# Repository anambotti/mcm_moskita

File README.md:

# pcb_16ccd_module
16-CCD module

# Create a newq branch 
git checkout -b branchName

# Move back to master branch
git checkout master

# List branches

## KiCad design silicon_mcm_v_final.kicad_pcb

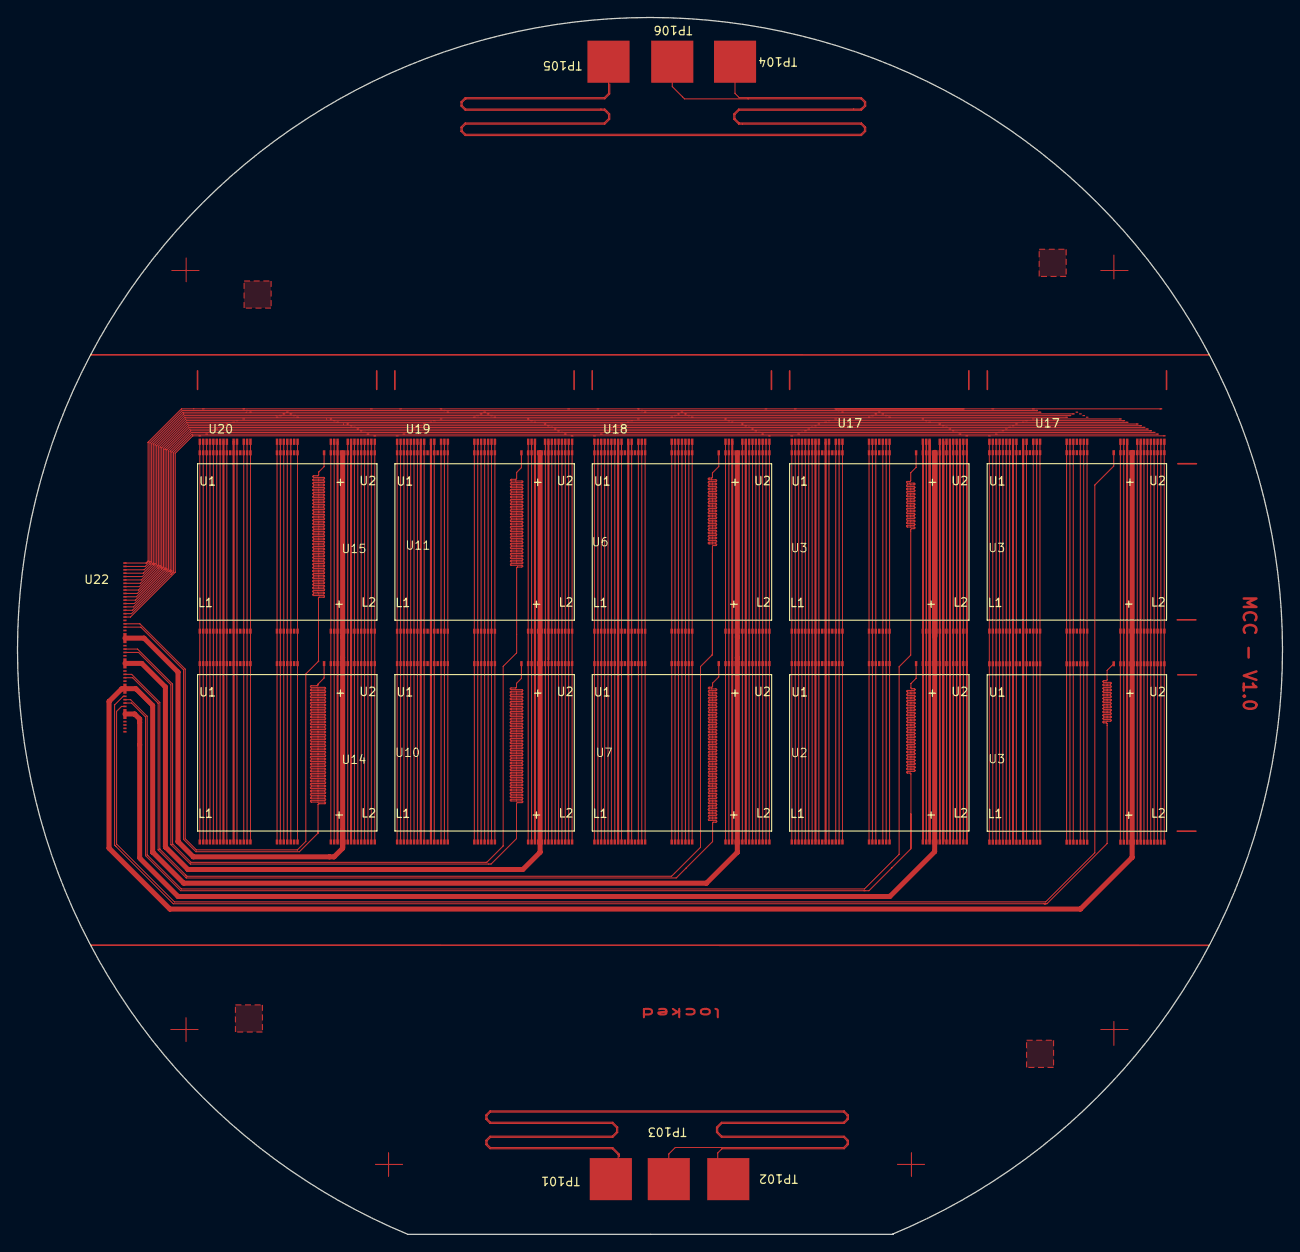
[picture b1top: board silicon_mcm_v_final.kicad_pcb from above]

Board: 2 copper layers, 150.0 x 144.3 mm, 22 parts (0 on the bottom side), 30 nets.

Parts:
TP101, TP102, TP103, TP104, TP105, TP106: silicon_test_pad; TEST-PAD
U2, U3, U3#2, U3#3, U6, U7, U10, U11, U14, U15: MC_1278x1058_pads_8Feb2021
U17, U17#2, U18, U19, U20: mcm_bus
U22: mcm_flex; mcm_flex_wide

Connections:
unnamed: TP101.1 (TESTPAD), TP102.1 (TESTPAD)
unnamed: TP104.1 (TESTPAD), TP105.1 (TESTPAD)
barrier: U2.75 (DS), U2.76 (DS), U2.77 (DS), U2.78 (DS), U3.75 (DS), U3.76 (DS), U3.77 (DS), U3.78 (DS), U3#2.75 (DS), U3#2.76 (DS), U3#2.77 (DS), U3#2.78 (DS), U3#3.75 (DS), U3#3.76 (DS), U3#3.77 (DS), U3#3.78 (DS), U6.75 (DS), U6.76 (DS), U6.77 (DS), U6.78 (DS), U7.75 (DS), U7.76 (DS), U7.77 (DS), U7.78 (DS), U10.75 (DS), U10.76 (DS), U10.77 (DS), U10.78 (DS), U11.75 (DS), U11.76 (DS), U11.77 (DS), U11.78 (DS), U14.75 (DS), U14.76 (DS), U14.77 (DS), U14.78 (DS), U15.75 (DS), U15.76 (DS), U15.77 (DS), U15.78 (DS), U17.17 (DS), U17#2.17 (DS), U18.17 (DS), U19.17 (DS), U20.17 (DS), U22.1 (barrier)
dg: U2.9 (DG-L2), U2.31 (DG-L1), U2.46 (DG-U1), U2.68 (DG-U2), U3.9 (DG-L2), U3.31 (DG-L1), U3.46 (DG-U1), U3.68 (DG-U2), U3#2.9 (DG-L2), U3#2.31 (DG-L1), U3#2.46 (DG-U1), U3#2.68 (DG-U2), U3#3.9 (DG-L2), U3#3.31 (DG-L1), U3#3.46 (DG-U1), U3#3.68 (DG-U2), U6.9 (DG-L2), U6.31 (DG-L1), U6.46 (DG-U1), U6.68 (DG-U2), U7.9 (DG-L2), U7.31 (DG-L1), U7.46 (DG-U1), U7.68 (DG-U2), U10.9 (DG-L2), U10.31 (DG-L1), U10.46 (DG-U1), U10.68 (DG-U2), U11.9 (DG-L2), U11.31 (DG-L1), U11.46 (DG-U1), U11.68 (DG-U2), U14.9 (DG-L2), U14.31 (DG-L1), U14.46 (DG-U1), U14.68 (DG-U2), U15.9 (DG-L2), U15.31 (DG-L1), U15.46 (DG-U1), U15.68 (DG-U2), U17.8 (dg), U17#2.8 (dg), U18.8 (dg), U19.8 (dg), U20.8 (dg), U22.10 (dg)
h1: U2.3 (H1-L2), U2.37 (H1-L1), U2.40 (H1-U1), U2.74 (H1-U2), U3.3 (H1-L2), U3.37 (H1-L1), U3.40 (H1-U1), U3.74 (H1-U2), U3#2.3 (H1-L2), U3#2.37 (H1-L1), U3#2.40 (H1-U1), U3#2.74 (H1-U2), U3#3.3 (H1-L2), U3#3.37 (H1-L1), U3#3.40 (H1-U1), U3#3.74 (H1-U2), U6.3 (H1-L2), U6.37 (H1-L1), U6.40 (H1-U1), U6.74 (H1-U2), U7.3 (H1-L2), U7.37 (H1-L1), U7.40 (H1-U1), U7.74 (H1-U2), U10.3 (H1-L2), U10.37 (H1-L1), U10.40 (H1-U1), U10.74 (H1-U2), U11.3 (H1-L2), U11.37 (H1-L1), U11.40 (H1-U1), U11.74 (H1-U2), U14.3 (H1-L2), U14.37 (H1-L1), U14.40 (H1-U1), U14.74 (H1-U2), U15.3 (H1-L2), U15.37 (H1-L1), U15.40 (H1-U1), U15.74 (H1-U2), U17.2 (h1), U17#2.2 (h1), U18.2 (h1), U19.2 (h1), U20.2 (h1), U22.16 (h1)
h2: U2.4 (H2-L2), U2.36 (H2-L1), U2.41 (H2-U1), U2.73 (H2-U2), U3.4 (H2-L2), U3.36 (H2-L1), U3.41 (H2-U1), U3.73 (H2-U2), U3#2.4 (H2-L2), U3#2.36 (H2-L1), U3#2.41 (H2-U1), U3#2.73 (H2-U2), U3#3.4 (H2-L2), U3#3.36 (H2-L1), U3#3.41 (H2-U1), U3#3.73 (H2-U2), U6.4 (H2-L2), U6.36 (H2-L1), U6.41 (H2-U1), U6.73 (H2-U2), U7.4 (H2-L2), U7.36 (H2-L1), U7.41 (H2-U1), U7.73 (H2-U2), U10.4 (H2-L2), U10.36 (H2-L1), U10.41 (H2-U1), U10.73 (H2-U2), U11.4 (H2-L2), U11.36 (H2-L1), U11.41 (H2-U1), U11.73 (H2-U2), U14.4 (H2-L2), U14.36 (H2-L1), U14.41 (H2-U1), U14.73 (H2-U2), U15.4 (H2-L2), U15.36 (H2-L1), U15.41 (H2-U1), U15.73 (H2-U2), U17.3 (h2), U17#2.3 (h2), U18.3 (h2), U19.3 (h2), U20.3 (h2), U22.15 (h2)
h3: U2.5 (H3-L2), U2.35 (H3-L1), U2.42 (H3-U1), U2.72 (H3-U2), U3.5 (H3-L2), U3.35 (H3-L1), U3.42 (H3-U1), U3.72 (H3-U2), U3#2.5 (H3-L2), U3#2.35 (H3-L1), U3#2.42 (H3-U1), U3#2.72 (H3-U2), U3#3.5 (H3-L2), U3#3.35 (H3-L1), U3#3.42 (H3-U1), U3#3.72 (H3-U2), U6.5 (H3-L2), U6.35 (H3-L1), U6.42 (H3-U1), U6.72 (H3-U2), U7.5 (H3-L2), U7.35 (H3-L1), U7.42 (H3-U1), U7.72 (H3-U2), U10.5 (H3-L2), U10.35 (H3-L1), U10.42 (H3-U1), U10.72 (H3-U2), U11.5 (H3-L2), U11.35 (H3-L1), U11.42 (H3-U1), U11.72 (H3-U2), U14.5 (H3-L2), U14.35 (H3-L1), U14.42 (H3-U1), U14.72 (H3-U2), U15.5 (H3-L2), U15.35 (H3-L1), U15.42 (H3-U1), U15.72 (H3-U2), U17.4 (h3), U17#2.4 (h3), U18.4 (h3), U19.4 (h3), U20.4 (h3), U22.14 (h3)
n+: U2.20 (N+-GUARD-L), U2.24 (N+-GUARD-L1), U2.53 (N+-GUARD-U1), U2.57 (N+-GUARD-U), U3.20 (N+-GUARD-L), U3.24 (N+-GUARD-L1), U3.53 (N+-GUARD-U1), U3.57 (N+-GUARD-U), U3#2.24 (N+-GUARD-L1), U3#2.53 (N+-GUARD-U1), U3#3.24 (N+-GUARD-L1), U3#3.53 (N+-GUARD-U1), U6.20 (N+-GUARD-L), U6.24 (N+-GUARD-L1), U6.53 (N+-GUARD-U1), U6.57 (N+-GUARD-U), U7.20 (N+-GUARD-L), U7.24 (N+-GUARD-L1), U7.53 (N+-GUARD-U1), U7.57 (N+-GUARD-U), U10.20 (N+-GUARD-L), U10.24 (N+-GUARD-L1), U10.53 (N+-GUARD-U1), U10.57 (N+-GUARD-U), U11.20 (N+-GUARD-L), U11.24 (N+-GUARD-L1), U11.53 (N+-GUARD-U1), U11.57 (N+-GUARD-U), U14.20 (N+-GUARD-L), U14.24 (N+-GUARD-L1), U14.53 (N+-GUARD-U1), U14.57 (N+-GUARD-U), U15.20 (N+-GUARD-L), U15.24 (N+-GUARD-L1), U15.53 (N+-GUARD-U1), U15.57 (N+-GUARD-U), U17.15 (n+), U17#2.15 (n+), U18.15 (n+), U19.15 (n+), U20.15 (n+), U22.3 (n+)
og: U2.7 (OG-L2), U2.33 (OG-L1), U2.44 (OG-U1), U2.70 (OG-U2), U3.7 (OG-L2), U3.33 (OG-L1), U3.44 (OG-U1), U3.70 (OG-U2), U3#2.7 (OG-L2), U3#2.33 (OG-L1), U3#2.44 (OG-U1), U3#2.70 (OG-U2), U3#3.7 (OG-L2), U3#3.33 (OG-L1), U3#3.44 (OG-U1), U3#3.70 (OG-U2), U6.7 (OG-L2), U6.33 (OG-L1), U6.44 (OG-U1), U6.70 (OG-U2), U7.7 (OG-L2), U7.33 (OG-L1), U7.44 (OG-U1), U7.70 (OG-U2), U10.7 (OG-L2), U10.33 (OG-L1), U10.44 (OG-U1), U10.70 (OG-U2), U11.7 (OG-L2), U11.33 (OG-L1), U11.44 (OG-U1), U11.70 (OG-U2), U14.7 (OG-L2), U14.33 (OG-L1), U14.44 (OG-U1), U14.70 (OG-U2), U15.7 (OG-L2), U15.33 (OG-L1), U15.44 (OG-U1), U15.70 (OG-U2), U17.6 (og), U17#2.6 (og), U18.6 (og), U19.6 (og), U20.6 (og), U22.12 (og)
p+: U2.25 (P+-GUARD-L1), U2.52 (P+-GUARD-U1), U3.25 (P+-GUARD-L1), U3.52 (P+-GUARD-U1), U3#2.25 (P+-GUARD-L1), U3#2.52 (P+-GUARD-U1), U3#3.25 (P+-GUARD-L1), U3#3.52 (P+-GUARD-U1), U6.25 (P+-GUARD-L1), U6.52 (P+-GUARD-U1), U7.25 (P+-GUARD-L1), U7.52 (P+-GUARD-U1), U10.25 (P+-GUARD-L1), U10.52 (P+-GUARD-U1), U11.25 (P+-GUARD-L1), U11.52 (P+-GUARD-U1), U14.25 (P+-GUARD-L1), U14.52 (P+-GUARD-U1), U15.25 (P+-GUARD-L1), U15.52 (P+-GUARD-U1), U17.16 (p+), U17#2.16 (p+), U18.16 (p+), U19.16 (p+), U20.16 (p+), U22.2 (p+)
rg: U2.12 (RG-L2), U2.28 (RG-L1), U2.49 (RG-U1), U2.65 (RG-U2), U3.12 (RG-L2), U3.28 (RG-L1), U3.49 (RG-U1), U3.65 (RG-U2), U3#2.12 (RG-L2), U3#2.28 (RG-L1), U3#2.49 (RG-U1), U3#2.65 (RG-U2), U3#3.12 (RG-L2), U3#3.28 (RG-L1), U3#3.49 (RG-U1), U3#3.65 (RG-U2), U6.12 (RG-L2), U6.28 (RG-L1), U6.49 (RG-U1), U6.65 (RG-U2), U7.12 (RG-L2), U7.28 (RG-L1), U7.49 (RG-U1), U7.65 (RG-U2), U10.12 (RG-L2), U10.28 (RG-L1), U10.49 (RG-U1), U10.65 (RG-U2), U11.12 (RG-L2), U11.28 (RG-L1), U11.49 (RG-U1), U11.65 (RG-U2), U14.12 (RG-L2), U14.28 (RG-L1), U14.49 (RG-U1), U14.65 (RG-U2), U15.12 (RG-L2), U15.28 (RG-L1), U15.49 (RG-U1), U15.65 (RG-U2), U17.10 (rg), U17#2.10 (rg), U18.10 (rg), U19.10 (rg), U20.10 (rg), U22.8 (rg)
sg: U2.6 (SW-L2), U2.34 (SW-L1), U2.43 (SW-U1), U2.71 (SW-U2), U3.6 (SW-L2), U3.34 (SW-L1), U3.43 (SW-U1), U3.71 (SW-U2), U3#2.6 (SW-L2), U3#2.34 (SW-L1), U3#2.43 (SW-U1), U3#2.71 (SW-U2), U3#3.6 (SW-L2), U3#3.34 (SW-L1), U3#3.43 (SW-U1), U3#3.71 (SW-U2), U6.6 (SW-L2), U6.34 (SW-L1), U6.43 (SW-U1), U6.71 (SW-U2), U7.6 (SW-L2), U7.34 (SW-L1), U7.43 (SW-U1), U7.71 (SW-U2), U10.6 (SW-L2), U10.34 (SW-L1), U10.43 (SW-U1), U10.71 (SW-U2), U11.6 (SW-L2), U11.34 (SW-L1), U11.43 (SW-U1), U11.71 (SW-U2), U14.6 (SW-L2), U14.34 (SW-L1), U14.43 (SW-U1), U14.71 (SW-U2), U15.6 (SW-L2), U15.34 (SW-L1), U15.43 (SW-U1), U15.71 (SW-U2), U17.5 (sg), U17#2.5 (sg), U18.5 (sg), U19.5 (sg), U20.5 (sg), U22.13 (sg)
tg: U2.14 (TG-L2), U2.26 (TG-L1), U2.51 (TG-U1), U2.63 (TG-U2), U3.14 (TG-L2), U3.26 (TG-L1), U3.51 (TG-U1), U3.63 (TG-U2), U3#2.14 (TG-L2), U3#2.26 (TG-L1), U3#2.51 (TG-U1), U3#2.63 (TG-U2), U3#3.14 (TG-L2), U3#3.26 (TG-L1), U3#3.51 (TG-U1), U3#3.63 (TG-U2), U6.14 (TG-L2), U6.26 (TG-L1), U6.51 (TG-U1), U6.63 (TG-U2), U7.14 (TG-L2), U7.26 (TG-L1), U7.51 (TG-U1), U7.63 (TG-U2), U10.14 (TG-L2), U10.26 (TG-L1), U10.51 (TG-U1), U10.63 (TG-U2), U11.14 (TG-L2), U11.26 (TG-L1), U11.51 (TG-U1), U11.63 (TG-U2), U14.14 (TG-L2), U14.26 (TG-L1), U14.51 (TG-U1), U14.63 (TG-U2), U15.14 (TG-L2), U15.26 (TG-L1), U15.51 (TG-U1), U15.63 (TG-U2), U17.11 (tg), U17#2.11 (tg), U18.11 (tg), U19.11 (tg), U20.11 (tg), U22.7 (tg)
v1: U2.17 (V1-L2), U2.23 (V1-L1), U2.54 (V1-U1), U2.60 (V1-U2), U3.17 (V1-L2), U3.23 (V1-L1), U3.54 (V1-U1), U3.60 (V1-U2), U3#2.17 (V1-L2), U3#2.23 (V1-L1), U3#2.54 (V1-U1), U3#2.60 (V1-U2), U3#3.17 (V1-L2), U3#3.23 (V1-L1), U3#3.54 (V1-U1), U3#3.60 (V1-U2), U6.17 (V1-L2), U6.23 (V1-L1), U6.54 (V1-U1), U6.60 (V1-U2), U7.17 (V1-L2), U7.23 (V1-L1), U7.54 (V1-U1), U7.60 (V1-U2), U10.17 (V1-L2), U10.23 (V1-L1), U10.54 (V1-U1), U10.60 (V1-U2), U11.17 (V1-L2), U11.23 (V1-L1), U11.54 (V1-U1), U11.60 (V1-U2), U14.17 (V1-L2), U14.23 (V1-L1), U14.54 (V1-U1), U14.60 (V1-U2), U15.17 (V1-L2), U15.23 (V1-L1), U15.54 (V1-U1), U15.60 (V1-U2), U17.12 (v1), U17#2.12 (v1), U18.12 (v1), U19.12 (v1), U20.12 (v1), U22.6 (v1)
v2: U2.18 (V2-L2), U2.22 (V2-L1), U2.55 (V2-U1), U2.59 (V2-U2), U3.18 (V2-L2), U3.22 (V2-L1), U3.55 (V2-U1), U3.59 (V2-U2), U3#2.18 (V2-L2), U3#2.22 (V2-L1), U3#2.55 (V2-U1), U3#2.59 (V2-U2), U3#3.18 (V2-L2), U3#3.22 (V2-L1), U3#3.55 (V2-U1), U3#3.59 (V2-U2), U6.18 (V2-L2), U6.22 (V2-L1), U6.55 (V2-U1), U6.59 (V2-U2), U7.18 (V2-L2), U7.22 (V2-L1), U7.55 (V2-U1), U7.59 (V2-U2), U10.18 (V2-L2), U10.22 (V2-L1), U10.55 (V2-U1), U10.59 (V2-U2), U11.18 (V2-L2), U11.22 (V2-L1), U11.55 (V2-U1), U11.59 (V2-U2), U14.18 (V2-L2), U14.22 (V2-L1), U14.55 (V2-U1), U14.59 (V2-U2), U15.18 (V2-L2), U15.22 (V2-L1), U15.55 (V2-U1), U15.59 (V2-U2), U17.13 (v2), U17#2.13 (v2), U18.13 (v2), U19.13 (v2), U20.13 (v2), U22.5 (v2)
v3: U2.19 (V3-L2), U2.21 (V3-L1), U2.56 (V3-U1), U2.58 (V3-U2), U3.19 (V3-L2), U3.21 (V3-L1), U3.56 (V3-U1), U3.58 (V3-U2), U3#2.19 (V3-L2), U3#2.21 (V3-L1), U3#2.56 (V3-U1), U3#2.58 (V3-U2), U3#3.19 (V3-L2), U3#3.21 (V3-L1), U3#3.56 (V3-U1), U3#3.58 (V3-U2), U6.19 (V3-L2), U6.21 (V3-L1), U6.56 (V3-U1), U6.58 (V3-U2), U7.19 (V3-L2), U7.21 (V3-L1), U7.56 (V3-U1), U7.58 (V3-U2), U10.19 (V3-L2), U10.21 (V3-L1), U10.56 (V3-U1), U10.58 (V3-U2), U11.19 (V3-L2), U11.21 (V3-L1), U11.56 (V3-U1), U11.58 (V3-U2), U14.19 (V3-L2), U14.21 (V3-L1), U14.56 (V3-U1), U14.58 (V3-U2), U15.19 (V3-L2), U15.21 (V3-L1), U15.56 (V3-U1), U15.58 (V3-U2), U17.14 (v3), U17#2.14 (v3), U18.14 (v3), U19.14 (v3), U20.14 (v3), U22.4 (v3)
vdd: U2.30 (VDD-L1), U2.47 (VDD-U1), U2.67 (VDD-U2), U3.30 (VDD-L1), U3.47 (VDD-U1), U3.67 (VDD-U2), U3#2.67 (VDD-U2), U3#3.67 (VDD-U2), U6.30 (VDD-L1), U6.47 (VDD-U1), U6.67 (VDD-U2), U7.30 (VDD-L1), U7.47 (VDD-U1), U7.67 (VDD-U2), U10.30 (VDD-L1), U10.47 (VDD-U1), U10.67 (VDD-U2), U11.30 (VDD-L1), U11.47 (VDD-U1), U11.67 (VDD-U2), U14.30 (VDD-L1), U14.47 (VDD-U1), U14.67 (VDD-U2), U15.30 (VDD-L1), U15.47 (VDD-U1), U15.67 (VDD-U2), U22.22 (vdd), U22.27 (vdd), U22.32 (vdd), U22.37 (vdd)
vdrain: U2.8 (DRAIN-L2), U2.32 (DRAIN-L1), U2.45 (DRAIN-U1), U2.69 (DRAIN-U2), U3.8 (DRAIN-L2), U3.32 (DRAIN-L1), U3.45 (DRAIN-U1), U3.69 (DRAIN-U2), U3#2.8 (DRAIN-L2), U3#2.32 (DRAIN-L1), U3#2.45 (DRAIN-U1), U3#2.69 (DRAIN-U2), U3#3.8 (DRAIN-L2), U3#3.32 (DRAIN-L1), U3#3.45 (DRAIN-U1), U3#3.69 (DRAIN-U2), U6.8 (DRAIN-L2), U6.32 (DRAIN-L1), U6.45 (DRAIN-U1), U6.69 (DRAIN-U2), U7.8 (DRAIN-L2), U7.32 (DRAIN-L1), U7.45 (DRAIN-U1), U7.69 (DRAIN-U2), U10.8 (DRAIN-L2), U10.32 (DRAIN-L1), U10.45 (DRAIN-U1), U10.69 (DRAIN-U2), U11.8 (DRAIN-L2), U11.32 (DRAIN-L1), U11.45 (DRAIN-U1), U11.69 (DRAIN-U2), U14.8 (DRAIN-L2), U14.32 (DRAIN-L1), U14.45 (DRAIN-U1), U14.69 (DRAIN-U2), U15.8 (DRAIN-L2), U15.32 (DRAIN-L1), U15.45 (DRAIN-U1), U15.69 (DRAIN-U2), U17.7 (vdrain), U17#2.7 (vdrain), U18.7 (vdrain), U19.7 (vdrain), U20.7 (vdrain), U22.11 (vdrain)
video11: U3#3.64 (VIDEO-U2), U22.36 (vid_16)
video12: U2.64 (VIDEO-U2), U22.35 (vid_15)
video13: U3.64 (VIDEO-U2), U22.34 (vid_14)
video14: U3#2.64 (VIDEO-U2), U22.33 (vid_13)
video22: U6.64 (VIDEO-U2), U22.29 (vid_10)
video23: U7.64 (VIDEO-U2), U22.30 (vid_11)
video32: U10.64 (VIDEO-U2), U22.25 (vid_7)
video33: U11.64 (VIDEO-U2), U22.24 (vid_6)
video42: U14.64 (VIDEO-U2), U22.20 (vid_3)
video43: U15.64 (VIDEO-U2), U22.19 (vid_2)
vref: U2.11 (RD-L2), U2.29 (RD-L1), U2.48 (RD-U1), U2.66 (RD-U2), U3.11 (RD-L2), U3.29 (RD-L1), U3.48 (RD-U1), U3.66 (RD-U2), U3#2.11 (RD-L2), U3#2.29 (RD-L1), U3#2.48 (RD-U1), U3#2.66 (RD-U2), U3#3.11 (RD-L2), U3#3.29 (RD-L1), U3#3.48 (RD-U1), U3#3.66 (RD-U2), U6.11 (RD-L2), U6.29 (RD-L1), U6.48 (RD-U1), U6.66 (RD-U2), U7.11 (RD-L2), U7.29 (RD-L1), U7.48 (RD-U1), U7.66 (RD-U2), U10.11 (RD-L2), U10.29 (RD-L1), U10.48 (RD-U1), U10.66 (RD-U2), U11.11 (RD-L2), U11.29 (RD-L1), U11.48 (RD-U1), U11.66 (RD-U2), U14.11 (RD-L2), U14.29 (RD-L1), U14.48 (RD-U1), U14.66 (RD-U2), U15.11 (RD-L2), U15.29 (RD-L1), U15.48 (RD-U1), U15.66 (RD-U2), U17.9 (vref), U17#2.9 (vref), U18.9 (vref), U19.9 (vref), U20.9 (vref), U22.9 (vref)
vsub: U2.1 (VSub), U2.2 (VSub), U2.38 (VSub), U2.39 (VSub), U3.1 (VSub), U3.2 (VSub), U3.38 (VSub), U3.39 (VSub), U3#2.1 (VSub), U3#2.2 (VSub), U3#2.38 (VSub), U3#2.39 (VSub), U3#3.1 (VSub), U3#3.2 (VSub), U3#3.38 (VSub), U3#3.39 (VSub), U6.1 (VSub), U6.2 (VSub), U6.38 (VSub), U6.39 (VSub), U7.1 (VSub), U7.2 (VSub), U7.38 (VSub), U7.39 (VSub), U10.1 (VSub), U10.2 (VSub), U10.38 (VSub), U10.39 (VSub), U11.1 (VSub), U11.2 (VSub), U11.38 (VSub), U11.39 (VSub), U14.1 (VSub), U14.2 (VSub), U14.38 (VSub), U14.39 (VSub), U15.1 (VSub), U15.2 (VSub), U15.38 (VSub), U15.39 (VSub), U17.1 (vsub), U17#2.1 (vsub), U18.1 (vsub), U19.1 (vsub), U20.1 (vsub), U22.17 (vsub)

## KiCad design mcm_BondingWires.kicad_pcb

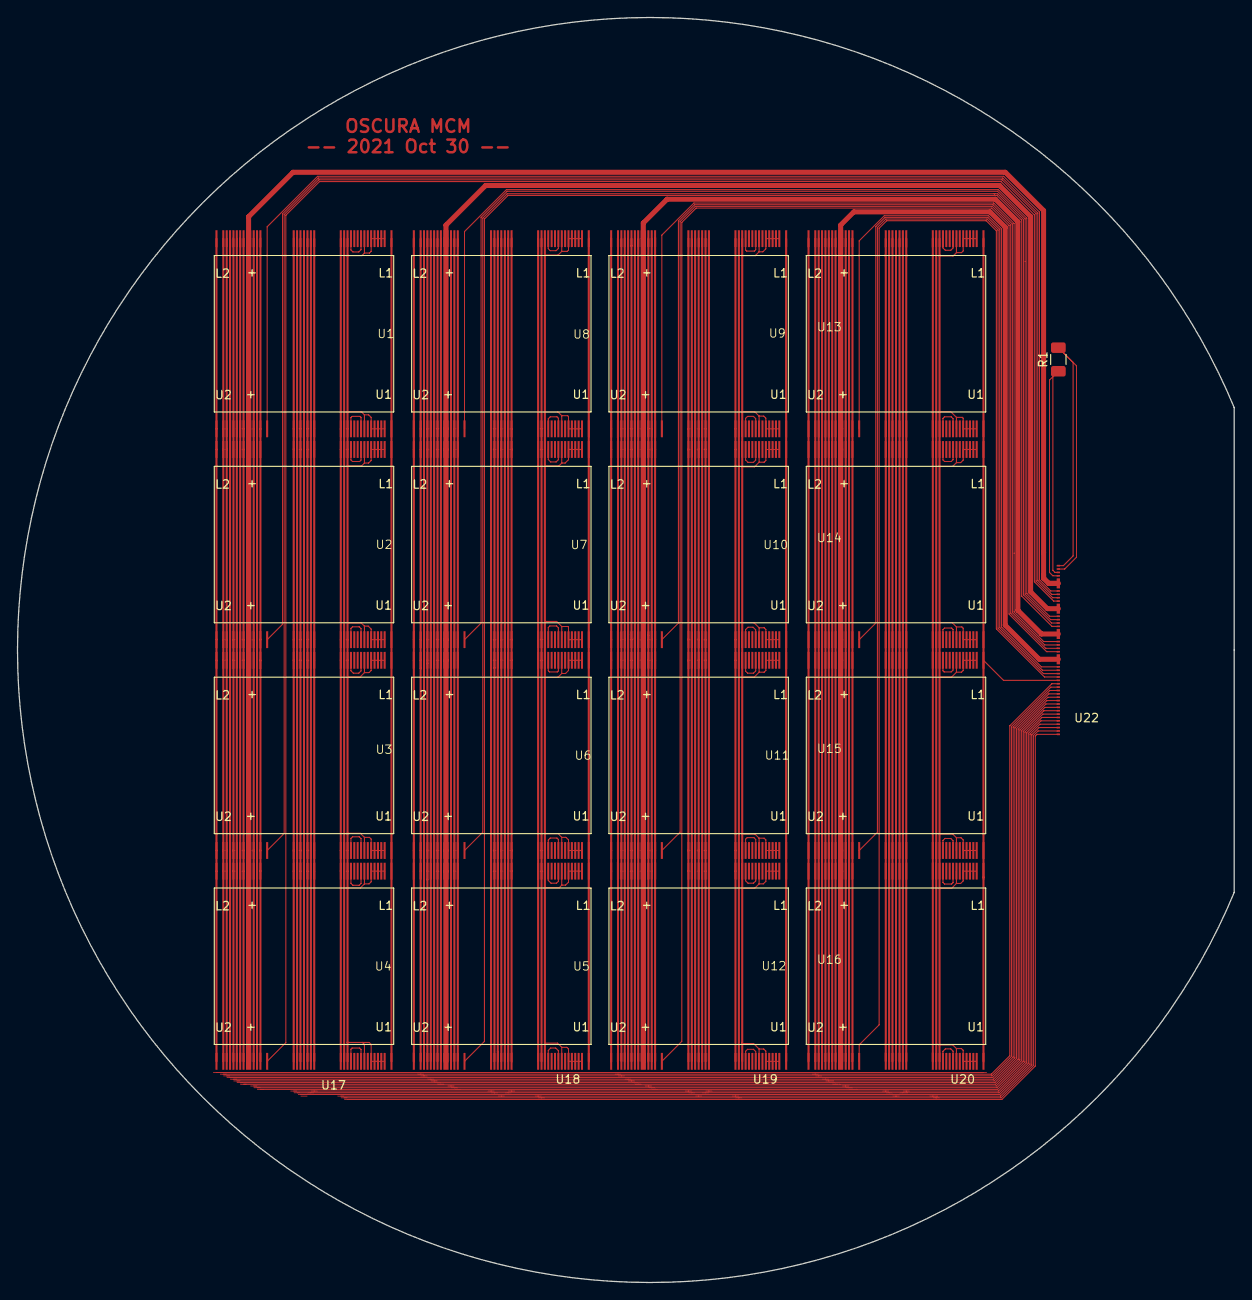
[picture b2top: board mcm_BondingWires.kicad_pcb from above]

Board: 2 copper layers, 144.3 x 150.0 mm, 22 parts (0 on the bottom side), 68 nets.

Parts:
R1: RTD-100; R_1206_3216Metric
U1, U2, U3, U4, U5, U6, U7, U8, U9, U10, U11, U12, U13, U14, U15, U16: MC_1278x1058_pads_8Feb2021
U17, U18, U19, U20: mcm_bus
U22: mcm_flex; mcm_flex_wide

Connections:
unnamed: R1.1, U22.38, U22.39
unnamed: R1.2, U22.40, U22.41
unnamed: U1.27, U1.30
unnamed: U1.47, U1.50
unnamed: U2.27, U2.30
unnamed: U2.47, U2.50
unnamed: U3.27, U3.30
unnamed: U3.47, U3.50
unnamed: U4.27, U4.30
unnamed: U4.47, U4.50
unnamed: U5.27, U5.30
unnamed: U5.47, U5.50
unnamed: U6.27, U6.30
unnamed: U6.47, U6.50
unnamed: U7.27, U7.30
unnamed: U7.47, U7.50
unnamed: U8.27, U8.30
unnamed: U8.47, U8.50
unnamed: U9.27, U9.30
unnamed: U9.47, U9.50
unnamed: U10.27, U10.30
unnamed: U10.47, U10.50
unnamed: U11.27, U11.30
unnamed: U11.47, U11.50
unnamed: U12.27, U12.30
unnamed: U12.47, U12.50
unnamed: U13.27, U13.30
unnamed: U13.47, U13.50
unnamed: U14.27, U14.30
unnamed: U14.47, U14.50
unnamed: U15.27, U15.30
unnamed: U15.47, U15.50
unnamed: U16.27, U16.30
unnamed: U16.47, U16.50
barrier: U1.26, U1.31, U1.33, U1.34, U1.35, U1.36, U1.37, U1.40, U1.41, U1.42, U1.43, U1.44, U1.46, U1.51, U2.26, U2.31, U2.33, U2.34, U2.35, U2.36, U2.37, U2.40, U2.41, U2.42, U2.43, U2.44, U2.46, U2.51, U3.26, U3.31, U3.33, U3.34, U3.35, U3.36, U3.37, U3.40, U3.41, U3.42, U3.43, U3.44, U3.46, U3.51, U4.26, U4.31, U4.33, U4.34, U4.35, U4.36, U4.37, U4.40, U4.41, U4.42, U4.43, U4.44, U4.46, U4.51, U5.26, U5.31, U5.33, U5.34, U5.35, U5.36, U5.37, U5.40, U5.41, U5.42, U5.43, U5.44, U5.46, U5.51, U6.26, U6.31, U6.33, U6.34, U6.35, U6.36, U6.37, U6.40, U6.41, U6.42, U6.43, U6.44, U6.46, U6.51, U7.26, U7.31, U7.33, U7.34, U7.35, U7.36, U7.37, U7.40, U7.41, U7.42, U7.43, U7.44, U7.46, U7.51, U8.26, U8.31, U8.33, U8.34, U8.35, U8.36, U8.37, U8.40, U8.41, U8.42, U8.43, U8.44, U8.46, U8.51, U9.26, U9.31, U9.33, U9.34, U9.35, U9.36, U9.37, U9.40, U9.41, U9.42, U9.43, U9.44, U9.46, U9.51, U10.26, U10.31, U10.33, U10.34, U10.35, U10.36, U10.37, U10.40, U10.41, U10.42, U10.43, U10.44, U10.46, U10.51, U11.26, U11.31, U11.33, U11.34, U11.35, U11.36, U11.37, U11.40, U11.41, U11.42, U11.43, U11.44, U11.46, U11.51, U12.26, U12.31, U12.33, U12.34, U12.35, U12.36, U12.37, U12.40, U12.41, U12.42, U12.43, U12.44, U12.46, U12.51, U13.26, U13.31, U13.33, U13.34, U13.35, U13.36, U13.37, U13.40, U13.41, U13.42, U13.43, U13.44, U13.46, U13.51, U14.26, U14.31, U14.33, U14.34, U14.35, U14.36, U14.37, U14.40, U14.41, U14.42, U14.43, U14.44, U14.46, U14.51, U15.26, U15.31, U15.33, U15.34, U15.35, U15.36, U15.37, U15.40, U15.41, U15.42, U15.43, U15.44, U15.46, U15.51, U16.26, U16.31, U16.33, U16.34, U16.35, U16.36, U16.37, U16.40, U16.41, U16.42, U16.43, U16.44, U16.46, U16.51, U17.17, U18.17, U19.17, U20.17, U22.1
dg: U1.9, U1.68, U2.9, U2.68, U3.9, U3.68, U4.9, U4.68, U5.9, U5.68, U6.9, U6.68, U7.9, U7.68, U8.9, U8.68, U9.9, U9.68, U10.9, U10.68, U11.9, U11.68, U12.9, U12.68, U13.9, U13.68, U14.9, U14.68, U15.9, U15.68, U16.9, U16.68, U17.8, U18.8, U19.8, U20.8, U22.10
h1: U1.3, U1.74, U2.3, U2.74, U3.3, U3.74, U4.3, U4.74, U5.3, U5.74, U6.3, U6.74, U7.3, U7.74, U8.3, U8.74, U9.3, U9.74, U10.3, U10.74, U11.3, U11.74, U12.3, U12.74, U13.3, U13.74, U14.3, U14.74, U15.3, U15.74, U16.3, U16.74, U17.2, U18.2, U19.2, U20.2, U22.16
h2: U1.4, U1.73, U2.4, U2.73, U3.4, U3.73, U4.4, U4.73, U5.4, U5.73, U6.4, U6.73, U7.4, U7.73, U8.4, U8.73, U9.4, U9.73, U10.4, U10.73, U11.4, U11.73, U12.4, U12.73, U13.4, U13.73, U14.4, U14.73, U15.4, U15.73, U16.4, U16.73, U17.3, U18.3, U19.3, U20.3, U22.15
h3: U1.5, U1.72, U2.5, U2.72, U3.5, U3.72, U4.5, U4.72, U5.5, U5.72, U6.5, U6.72, U7.5, U7.72, U8.5, U8.72, U9.5, U9.72, U10.5, U10.72, U11.5, U11.72, U12.5, U12.72, U13.5, U13.72, U14.5, U14.72, U15.5, U15.72, U16.5, U16.72, U17.4, U18.4, U19.4, U20.4, U22.14
n+: U1.20, U1.24, U1.53, U1.57, U2.20, U2.24, U2.53, U2.57, U3.20, U3.24, U3.53, U3.57, U4.20, U4.24, U4.53, U4.57, U5.20, U5.24, U5.53, U5.57, U6.20, U6.24, U6.53, U6.57, U7.20, U7.24, U7.53, U7.57, U8.20, U8.24, U8.53, U8.57, U9.20, U9.24, U9.53, U9.57, U10.20, U10.24, U10.53, U10.57, U11.20, U11.24, U11.53, U11.57, U12.20, U12.24, U12.53, U12.57, U13.20, U13.24, U13.53, U13.57, U14.20, U14.24, U14.53, U14.57, U15.20, U15.24, U15.53, U15.57, U16.20, U16.24, U16.53, U16.57, U17.15, U18.15, U19.15, U20.15, U22.3
og: U1.7, U1.70, U2.7, U2.70, U3.7, U3.70, U4.7, U4.70, U5.7, U5.70, U6.7, U6.70, U7.7, U7.70, U8.7, U8.70, U9.7, U9.70, U10.7, U10.70, U11.7, U11.70, U12.7, U12.70, U13.7, U13.70, U14.7, U14.70, U15.7, U15.70, U16.7, U16.70, U17.6, U18.6, U19.6, U20.6, U22.12
p+: U1.25, U1.52, U2.25, U2.52, U3.25, U3.52, U4.25, U4.52, U5.25, U5.52, U6.25, U6.52, U7.25, U7.52, U8.25, U8.52, U9.25, U9.52, U10.25, U10.52, U11.25, U11.52, U12.25, U12.52, U13.25, U13.52, U14.25, U14.52, U15.25, U15.52, U16.25, U16.52, U17.16, U18.16, U19.16, U20.16, U22.2
rg: U1.12, U1.65, U2.12, U2.65, U3.12, U3.65, U4.12, U4.65, U5.12, U5.65, U6.12, U6.65, U7.12, U7.65, U8.12, U8.65, U9.12, U9.65, U10.12, U10.65, U11.12, U11.65, U12.12, U12.65, U13.12, U13.65, U14.12, U14.65, U15.12, U15.65, U16.12, U16.65, U17.10, U18.10, U19.10, U20.10, U22.8
sg: U1.6, U1.71, U2.6, U2.71, U3.6, U3.71, U4.6, U4.71, U5.6, U5.71, U6.6, U6.71, U7.6, U7.71, U8.6, U8.71, U9.6, U9.71, U10.6, U10.71, U11.6, U11.71, U12.6, U12.71, U13.6, U13.71, U14.6, U14.71, U15.6, U15.71, U16.6, U16.71, U17.5, U18.5, U19.5, U20.5, U22.13
tg: U1.14, U1.63, U2.14, U2.63, U3.14, U3.63, U4.14, U4.63, U5.14, U5.63, U6.14, U6.63, U7.14, U7.63, U8.14, U8.63, U9.14, U9.63, U10.14, U10.63, U11.14, U11.63, U12.14, U12.63, U13.14, U13.63, U14.14, U14.63, U15.14, U15.63, U16.14, U16.63, U17.11, U18.11, U19.11, U20.11, U22.7
v1: U1.17, U1.23, U1.54, U1.60, U2.17, U2.23, U2.54, U2.60, U3.17, U3.23, U3.54, U3.60, U4.17, U4.23, U4.54, U4.60, U5.17, U5.23, U5.54, U5.60, U6.17, U6.23, U6.54, U6.60, U7.17, U7.23, U7.54, U7.60, U8.17, U8.23, U8.54, U8.60, U9.17, U9.23, U9.54, U9.60, U10.17, U10.23, U10.54, U10.60, U11.17, U11.23, U11.54, U11.60, U12.17, U12.23, U12.54, U12.60, U13.17, U13.23, U13.54, U13.60, U14.17, U14.23, U14.54, U14.60, U15.17, U15.23, U15.54, U15.60, U16.17, U16.23, U16.54, U16.60, U17.12, U18.12, U19.12, U20.12, U22.6
v2: U1.18, U1.22, U1.55, U1.59, U2.18, U2.22, U2.55, U2.59, U3.18, U3.22, U3.55, U3.59, U4.18, U4.22, U4.55, U4.59, U5.18, U5.22, U5.55, U5.59, U6.18, U6.22, U6.55, U6.59, U7.18, U7.22, U7.55, U7.59, U8.18, U8.22, U8.55, U8.59, U9.18, U9.22, U9.55, U9.59, U10.18, U10.22, U10.55, U10.59, U11.18, U11.22, U11.55, U11.59, U12.18, U12.22, U12.55, U12.59, U13.18, U13.22, U13.55, U13.59, U14.18, U14.22, U14.55, U14.59, U15.18, U15.22, U15.55, U15.59, U16.18, U16.22, U16.55, U16.59, U17.13, U18.13, U19.13, U20.13, U22.5
v3: U1.19, U1.21, U1.56, U1.58, U2.19, U2.21, U2.56, U2.58, U3.19, U3.21, U3.56, U3.58, U4.19, U4.21, U4.56, U4.58, U5.19, U5.21, U5.56, U5.58, U6.19, U6.21, U6.56, U6.58, U7.19, U7.21, U7.56, U7.58, U8.19, U8.21, U8.56, U8.58, U9.19, U9.21, U9.56, U9.58, U10.19, U10.21, U10.56, U10.58, U11.19, U11.21, U11.56, U11.58, U12.19, U12.21, U12.56, U12.58, U13.19, U13.21, U13.56, U13.58, U14.19, U14.21, U14.56, U14.58, U15.19, U15.21, U15.56, U15.58, U16.19, U16.21, U16.56, U16.58, U17.14, U18.14, U19.14, U20.14, U22.4
vdd: U1.67, U2.67, U3.67, U4.67, U5.67, U6.67, U7.67, U8.67, U9.67, U10.67, U11.67, U12.67, U13.67, U14.67, U15.67, U16.67, U22.22, U22.27, U22.32, U22.37
vdrain: U1.8, U1.69, U2.8, U2.69, U3.8, U3.69, U4.8, U4.69, U5.8, U5.69, U6.8, U6.69, U7.8, U7.69, U8.8, U8.69, U9.8, U9.69, U10.8, U10.69, U11.8, U11.69, U12.8, U12.69, U13.8, U13.69, U14.8, U14.69, U15.8, U15.69, U16.8, U16.69, U17.7, U18.7, U19.7, U20.7, U22.11
video11: U1.64, U22.36
video12: U2.64, U22.35
video13: U3.64, U22.34
video14: U4.64, U22.33
video21: U5.64, U22.28
video22: U6.64, U22.29
video23: U7.64, U22.30
video24: U8.64, U22.31
video31: U9.64, U22.26
video32: U10.64, U22.25
video33: U11.64, U22.24
video34: U12.64, U22.23
video41: U13.64, U22.21
video42: U14.64, U22.20
video43: U15.64, U22.19
video44: U16.64, U22.18
vref: U1.11, U1.66, U2.11, U2.66, U3.11, U3.66, U4.11, U4.66, U5.11, U5.66, U6.11, U6.66, U7.11, U7.66, U8.11, U8.66, U9.11, U9.66, U10.11, U10.66, U11.11, U11.66, U12.11, U12.66, U13.11, U13.66, U14.11, U14.66, U15.11, U15.66, U16.11, U16.66, U17.9, U18.9, U19.9, U20.9, U22.9
vsub: U1.1, U1.2, U1.38, U1.39, U2.1, U2.2, U2.38, U2.39, U3.1, U3.2, U3.38, U3.39, U4.1, U4.2, U4.38, U4.39, U5.1, U5.2, U5.38, U5.39, U6.1, U6.2, U6.38, U6.39, U7.1, U7.2, U7.38, U7.39, U8.1, U8.2, U8.38, U8.39, U9.1, U9.2, U9.38, U9.39, U10.1, U10.2, U10.38, U10.39, U11.1, U11.2, U11.38, U11.39, U12.1, U12.2, U12.38, U12.39, U13.1, U13.2, U13.38, U13.39, U14.1, U14.2, U14.38, U14.39, U15.1, U15.2, U15.38, U15.39, U16.1, U16.2, U16.38, U16.39, U17.1, U18.1, U19.1, U20.1, U22.17
